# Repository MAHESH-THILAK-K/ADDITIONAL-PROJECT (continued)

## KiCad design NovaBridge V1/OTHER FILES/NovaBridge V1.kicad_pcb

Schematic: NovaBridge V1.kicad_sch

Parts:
C1: 10uF; C_1206_3216Metric_Pad1.33x1.80mm_HandSolder
C2: 22uF; C_1206_3216Metric_Pad1.33x1.80mm_HandSolder
C3: 100nF; C_1206_3216Metric_Pad1.33x1.80mm_HandSolder
D1: LED; LED_1206_3216Metric_Pad1.42x1.75mm_HandSolder
J1, J2: Conn_02x09_Odd_Even; PinSocket_2x09_P2.54mm_Vertical
J3, J4: Conn_01x08_Female; PinSocket_1x08_P2.54mm_Vertical
J5: +/- rail; PinHeader_2x06_P2.54mm_Vertical
J6: Conn_01x03; PinHeader_1x03_P2.54mm_Vertical
Q1: MUN5214DW1; SOT-363_SC-70-6
R1: 2k; R_1206_3216Metric_Pad1.30x1.75mm_HandSolder
U1: AZ1117; SOT-223-3_TabPin2

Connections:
/#SU: J3.7
/+3.3v: J3.2
/+5v-in: J3.1, J6.1
/+5v-out: C1.1, J6.2, R1.2, U1.3 (VI)
/CLK: J1.15
/CMD: J1.16
/CTS: J4.8
/DCD: J4.2
/DSR: J4.4
/DTR: J4.3, Q1.1 (E1), Q1.5 (B2)
/ESP-RX: J2.13, J4.5
/ESP-TX: J2.15, J4.6
/GND: C1.2, C2.2, C3.2, D1.1 (K), J2.11, J2.18, J3.3, J5.2, J5.4, J5.6, J5.8, J5.10, J5.12, U1.1 (ADJ)
/IO2: J2.1
/IO4: J2.3
/IO5: J2.8
/IO12: J1.12
/IO13: J1.11
/IO14: J1.9
/IO15: J2.2
/IO16: J2.6
/IO17: J2.5
/IO18: J2.7
/IO19: J2.10
/IO21: J2.9
/IO22: J2.12
/IO23: J2.14
/IO25: J1.8
/IO26: J1.7
/IO27: J1.10
/IO32: J1.6
/IO33: J1.5
/IO34: J1.4
/IO35: J1.3
/R1: J4.1
/RST: J3.4
/RTS: J4.7, Q1.2 (B1), Q1.4 (E2)
/SD1: J1.17
/SD2: J1.14
/SD3: J1.13
/SDO: J1.18
/SU: J3.8
/SVN: J1.1
/SVP: J1.2
/VDD: C2.1, J2.17, J5.1, J5.3, J5.5, J5.7, J5.9, J5.11, U1.2 (VO)
/aIO2: J3.6
/aIO3: J3.5
unnamed: D1.2 (A), R1.1

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
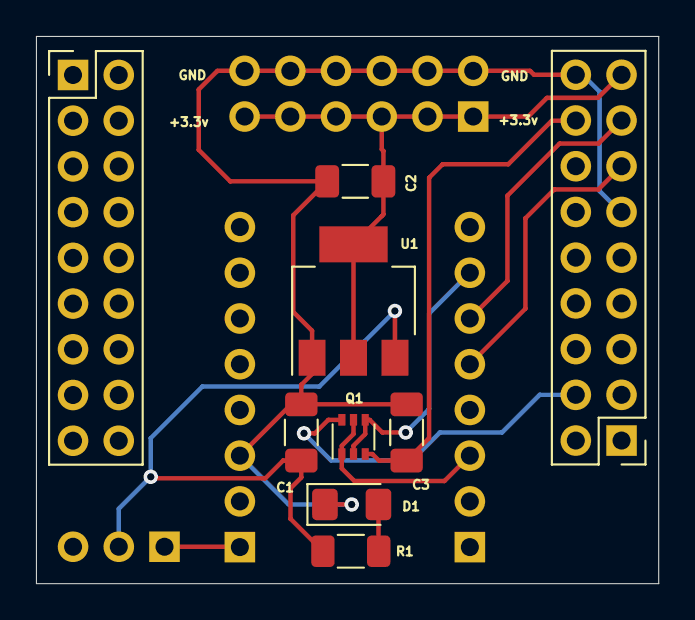
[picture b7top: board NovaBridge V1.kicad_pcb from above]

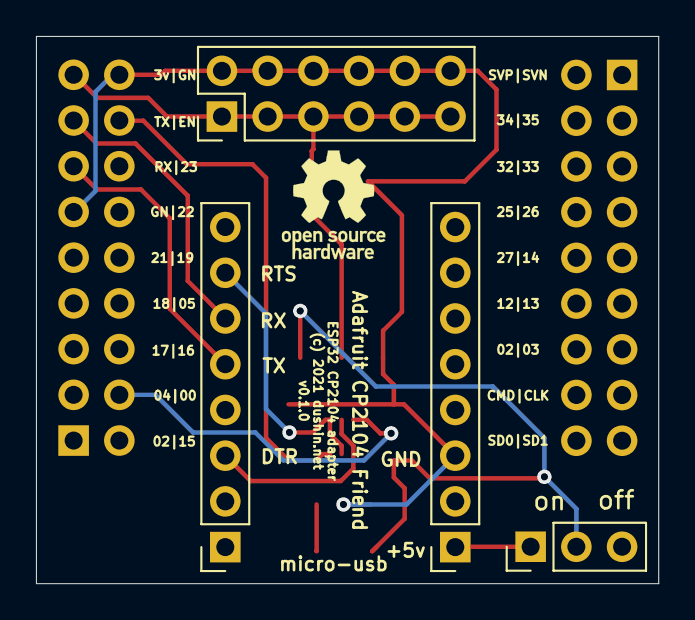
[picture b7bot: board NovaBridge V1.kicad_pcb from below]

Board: 2 copper layers, 34.6 x 30.4 mm, 13 parts (4 on the bottom side), 11 nets.

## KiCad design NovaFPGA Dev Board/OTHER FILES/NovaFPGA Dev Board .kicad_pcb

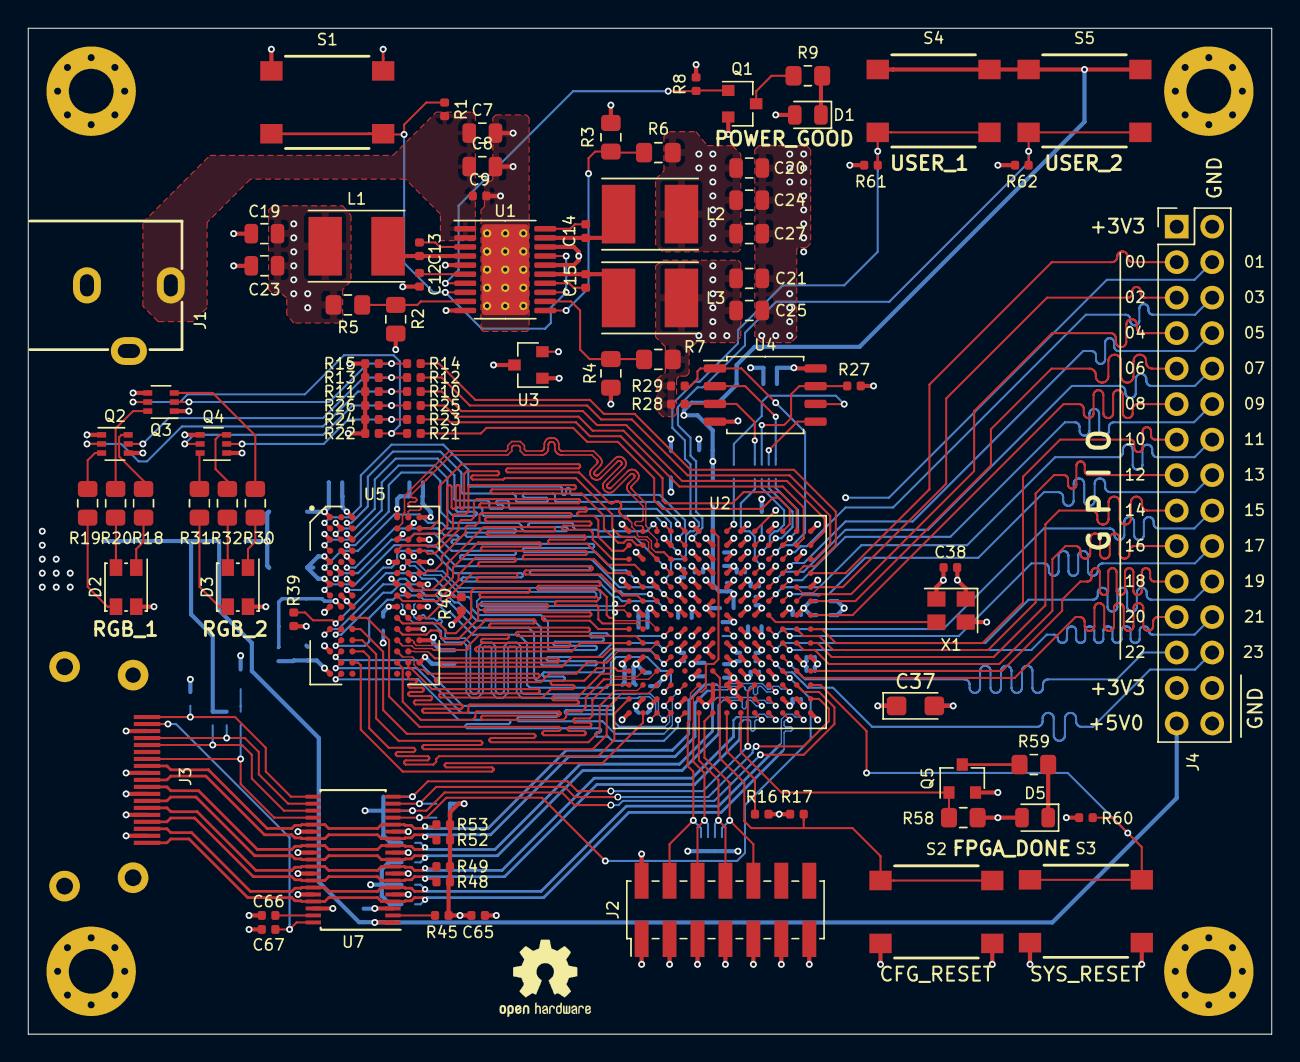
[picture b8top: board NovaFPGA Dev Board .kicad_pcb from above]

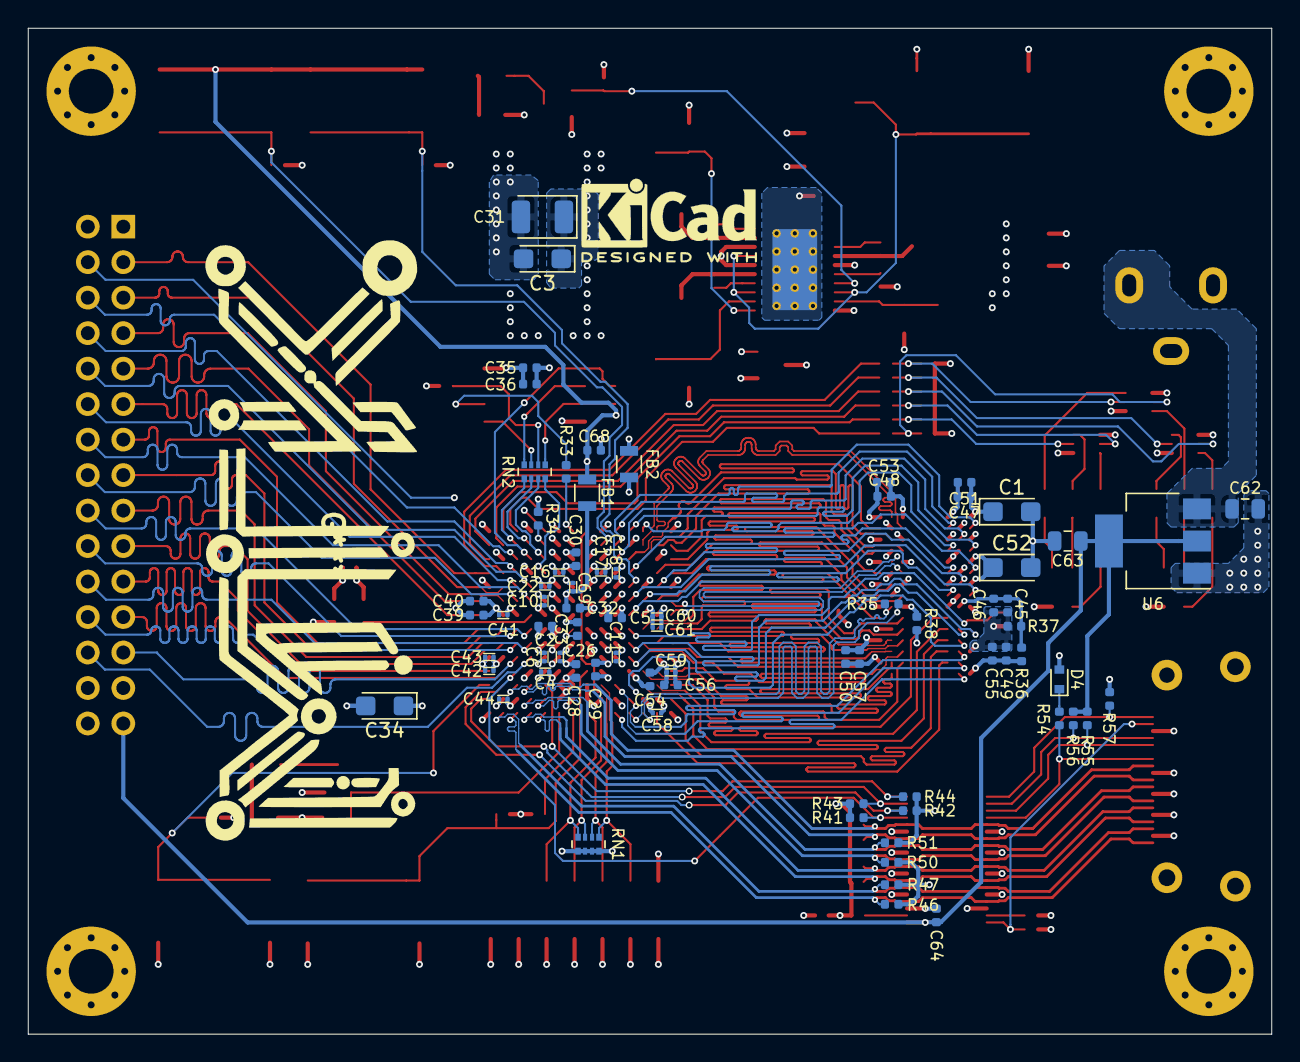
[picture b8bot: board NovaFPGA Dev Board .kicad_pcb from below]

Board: 4 copper layers, 89.0 x 72.0 mm, 169 parts (74 on the bottom side), 164 nets.

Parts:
C1, C3, C34, C37, C52: 47 uF; CP_EIA-3216-18_Kemet-A
C2, C5, C28, C29, C30, C39, C40, C54, C56, C68: 4.7 uF; C_0402_1005Metric
C4, C6, C10, C11, C16, C17, C18, C22, C26, C41, C42, C43, C44, C58, C59, C60, C61, C69: 0.47 uF; C_0201_0603Metric
C7, C8, C62: 10 uF; C_0805_2012Metric
C9, C13, C14, C15, C32, C33, C35, C38, C45, C47, C48, C49, C50, C64, C65, C66, C67: 0.1 uF; C_0402_1005Metric
C12, C36, C51, C53, C55, C57: 1 uF; C_0402_1005Metric
C19, C20, C21, C23, C24, C25, C27, C63: 22 uF; C_0805_2012Metric
C31: 100 uF; CP_EIA-3528-15_AVX-H
C46: 10 nF; C_0402_1005Metric
D1: POWER_GOOD; LED_0805_2012Metric
D2, D3: LED_RAGB; LED_Kingbright_AAA3528ESGCT
D4: BAS16XV2T1G; D_SOD-523
D5: FPGA_DONE; LED_0805_2012Metric
FB1, FB2: 600R; L_0805
H1, H2, H3, H4: MountingHole_Pad; MountingHole_3.2mm_M3_Pad_Via
J1: Barrel_Jack_Switch; PJ_102B
J2: XILINX_JTAG; PinHeader_2x07_P2.00mm_Vertical_SMD
J3: HDMI_A; hdmi_type_a_10029449-111RLF
J4: Conn_02x15_Odd_Even; PinHeader_2x15_P2.54mm_Vertical
L1, L2, L3: 2.2 uH; L_Taiyo-Yuden_NR-50xx_HandSoldering
Q1, Q5: DMN2020L; SOT-23
Q2, Q3, Q4: DMN63D8LDW; SOT-363_SC-70-6
R1, R8, R44: 100K; R_0402_1005Metric
R2, R3, R4: 2.2K; R_0805_2012Metric_Pad1.15x1.40mm_HandSolder
R5: 3.0K; R_0805_2012Metric_Pad1.15x1.40mm_HandSolder
R6, R9, R18, R30, R59: 680; R_0805_2012Metric_Pad1.15x1.40mm_HandSolder
R7: 7.36K; R_0805_2012Metric_Pad1.15x1.40mm_HandSolder
R10, R12, R14, R21, R23, R25, R55, R56: 2.2K; R_0402_1005Metric
R11, R13, R15, R22, R24, R26, R45, R57: 10K; R_0402_1005Metric
R16, R17, R27, R28, R29, R34, R38, R39, R40, R60, R61, R62: 4.75K; R_0402_1005Metric
R19, R20, R31, R32, R58: 330; R_0805_2012Metric_Pad1.15x1.40mm_HandSolder
R33, R46, R47, R48, R49, R50, R51, R52, R53: 49.9; R_0402_1005Metric
R35: 100; R_0402_1005Metric
R36, R37: 1.0K; R_0402_1005Metric
R41, R42, R43: 47K; R_0402_1005Metric
R54: 27K; R_0402_1005Metric
RN1: 10K; R_Array_Convex_4x0402
RN2: 49.9; R_Array_Convex_4x0402
S1: PWR_OFF; B3FS_1010P
S2: CFG_RESET; B3FS_1010P
S3: SYS_RESET; B3FS_1010P
S4: USER_1; B3FS_1010P
S5: USER_2; B3FS_1010P
U1: TPS65581; HTSSOP-20-1EP_4.4x6.5mm_P0.65mm_EP3.4x6.5mm_Mask2.75x3.43mm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
U2: XC7S50-FTGB196; Xilinx_FTGB196
U3: REF3012; SOT-23
U4: QSPI_Flash_SOIC8; SOIC-8_5.275x5.275mm_P1.27mm
U5: MT47H128M16XX; BGA-84_9x15_9.0x12.5mm
U6: AZ1117-5.0; SOT-223-3_TabPin2
U7: TPD12S521; TSSOP-38_4.4x9.7mm_P0.5mm
X1: DSC61XX; Oscillator_SMD_Abracon_ASE-4Pin_3.2x2.5mm

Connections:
+1V0: C3.1, C5.1, C11.1, C16.1, C17.1, C18.1, C20.1, C22.1, C24.1, C26.1, C27.1, C28.1, C29.1, C30.1, C31.1, L2.2, R6.1, U2.D6, U2.D8, U2.E5, U2.E7, U2.E9, U2.F6, U2.G5, U2.G9, U2.H6, U2.J5, U2.J9, U2.K6, U2.K8
+1V8: C1.1, C2.1, C4.1, C6.1, C10.1, C19.1, C23.1, C47.1, C48.1, C49.1, C50.1, C51.1, C52.1, C53.1, C54.1, C55.1, C56.1, C57.1, C58.1, C59.1, C60.1, C61.1, C68.1, FB1.2, L1.2, R5.1, R36.2, S4.1, S4.2, S5.1, S5.2, U2.F10, U2.G2, U2.H10, U2.K2, U2.K10, U2.L9, U2.N2, U5.A1, U5.A9, U5.C1, U5.C3, U5.C7, U5.C9, U5.E1, U5.E9, U5.G1, U5.G3, U5.G7, U5.G9, U5.J1, U5.J9, U5.M9, U5.R1
+1V8A: C32.1, C69.1, FB1.1, U2.F8
+3V3: C21.1, C25.1, C34.1, C35.1, C36.1, C37.1, C38.1, C39.1, C40.1, C41.1, C42.1, C43.1, C44.1, C65.1, D1.2, D2.2, D3.2, D4.2, D5.2, J2.2, J4.1, J4.27, L3.2, R7.1, R8.2, R16.2, R17.2, R27.2, R28.2, R29.2, R34.1, R41.1, R42.1, R43.1, R44.1, R45.2, R46.1, R47.1, R48.1, R49.1, R50.1, R51.1, R52.1, R53.1, R58.2, R60.1, RN1.5, RN1.6, RN1.7, RN1.8, U2.G13, U2.K13, U2.M7, U2.N6, U2.N7, U2.N8, U2.N13, U3.1, U4.8, X1.1, X1.4
+5V: C63.1, C64.1, J4.29, R55.2, R56.2, U6.2, U7.1
+12V: C7.1, C8.1, C9.1, C62.2, J1.1, R1.2, U1.1, U1.2, U6.3
/Bank0_14/FPGA_DONE: Q5.1, R58.1, U2.P9
/Bank0_14/FPGA_PUDC: R34.2, U2.B10
/Bank0_14/INIT_B: R16.1, U2.P8
/Bank0_14/JTAG_TCK: J2.6, RN1.2, U2.A7
/Bank0_14/JTAG_TDI: J2.10, RN1.4, U2.P7
/Bank0_14/JTAG_TDO: J2.8, RN1.3, U2.P6
/Bank0_14/JTAG_TMS: J2.4, RN1.1, U2.M6
/Bank0_14/PROGRAM_B: R17.1, S2.1, S2.2, U2.L7
/Bank0_14/RGB1_B: R14.2, U2.D13
/Bank0_14/RGB1_G: R12.2, U2.C14
/Bank0_14/RGB1_R: R10.2, U2.B14
/Bank0_14/RGB2_B: R25.2, U2.B13
/Bank0_14/RGB2_G: R23.2, U2.A13
/Bank0_14/RGB2_R: R21.2, U2.A12
/Bank0_14/SPI_CS: R29.1, U2.C11, U4.1
/Bank0_14/SPI_DQ0: RN2.3, U4.5
/Bank0_14/SPI_DQ1: RN2.4, U4.2
/Bank0_14/SPI_DQ2: R28.1, RN2.1, U4.3
/Bank0_14/SPI_DQ3: R27.1, RN2.2, U4.7
/Bank0_14/SPI_F_DQ0: RN2.6, U2.B11
/Bank0_14/SPI_F_DQ1: RN2.5, U2.B12
/Bank0_14/SPI_F_DQ2: RN2.8, U2.D10
/Bank0_14/SPI_F_DQ3: RN2.7, U2.C10
/Bank0_14/SPI_F_SCLK: R33.1, U2.A8
/Bank0_14/SPI_SCLK: R33.2, U4.6
/Bank0_14/SYSCLK: U2.G11, X1.3
/Bank0_14/SYSRESET: R60.2, S3.1, S3.2, U2.M14
/Bank34/DDR2_A0: U2.J2, U5.M8
/Bank34/DDR2_A1: U2.M3, U5.M3
/Bank34/DDR2_A2: U2.J1, U5.M7
/Bank34/DDR2_A3: U2.N4, U5.N2
/Bank34/DDR2_A4: U2.J3, U5.N8
/Bank34/DDR2_A5: U2.N1, U5.N3
/Bank34/DDR2_A6: U2.K3, U5.N7
/Bank34/DDR2_A7: U2.M5, U5.P2
/Bank34/DDR2_A8: U2.L1, U5.P8
/Bank34/DDR2_A9: U2.P2, U5.P3
/Bank34/DDR2_A10: U2.M4, U5.M2
/Bank34/DDR2_A11: U2.L3, U5.P7
/Bank34/DDR2_A12: U2.P5, U5.R2
/Bank34/DDR2_A13: U2.L2, U5.R8
/Bank34/DDR2_BA0: U2.K4, U5.L2
/Bank34/DDR2_BA1: U2.M2, U5.L3
/Bank34/DDR2_BA2: U2.J4, U5.L1
/Bank34/DDR2_CAS: U2.H1, U5.L7
/Bank34/DDR2_CK+: R35.1, U2.P4, U5.J8
/Bank34/DDR2_CK-: R35.2, U2.P3, U5.K8
/Bank34/DDR2_CKE: R39.2, U2.H4, U5.K2
/Bank34/DDR2_DM0: U2.E2, U5.F3
/Bank34/DDR2_DM1: U2.A5, U5.B3
/Bank34/DDR2_DQ0: U2.D2, U5.G8
/Bank34/DDR2_DQ1: U2.F4, U5.G2
/Bank34/DDR2_DQ2: U2.F2, U5.H7
/Bank34/DDR2_DQ3: U2.G4, U5.H3
/Bank34/DDR2_DQ4: U2.F3, U5.H1
/Bank34/DDR2_DQ5: U2.D1, U5.H9
/Bank34/DDR2_DQ6: U2.D4, U5.F1
/Bank34/DDR2_DQ7: U2.C1, U5.F9
/Bank34/DDR2_DQ8: U2.C3, U5.C8
/Bank34/DDR2_DQ9: U2.C5, U5.C2
/Bank34/DDR2_DQ10: U2.B2, U5.D7
/Bank34/DDR2_DQ11: U2.A3, U5.D3
/Bank34/DDR2_DQ12: U2.A4, U5.D1
/Bank34/DDR2_DQ13: U2.B1, U5.D9
/Bank34/DDR2_DQ14: U2.B5, U5.B1
/Bank34/DDR2_DQ15: U2.C4, U5.B9
/Bank34/DDR2_DQS0+: U2.G1, U5.F7
/Bank34/DDR2_DQS0-: U2.F1, U5.E8
/Bank34/DDR2_DQS1+: U2.B3, U5.B7
/Bank34/DDR2_DQS1-: U2.A2, U5.A8
/Bank34/DDR2_ODT: R40.2, U2.H3, U5.K9
/Bank34/DDR2_RAS: U2.H2, U5.K7
/Bank34/DDR2_WE: U2.M1, U5.K3
/Bank34/USER_1: R61.1, S4.3, S4.4, U2.E4
/Bank34/USER_2: R62.1, S5.3, S5.4, U2.B6
/Externals/HDMI_C_5V: C67.2, J3.18, U7.38
/Externals/HDMI_C_CEC: J3.13, R54.1, U7.23
/Externals/HDMI_C_HPD: J3.19, R57.1, U7.20
/Externals/HDMI_C_SCL: J3.15, R55.1, U7.22
/Externals/HDMI_C_SDA: J3.16, R56.1, U7.21
/Power/PGOOD: Q1.1, R8.1, U1.7
/Power/SW1: C13.1, L1.1, U1.4
/Power/SW2: C14.1, L2.1, U1.19
/Power/SW3: C15.1, L3.1, U1.15
ADC_REF: C33.1, U2.H8, U3.2
GND: C1.2, C2.2, C3.2, C4.2, C5.2, C6.2, C7.2, C8.2, C9.2, C10.2, C11.2, C12.2, C16.2, C17.2, C18.2, C19.2, C20.2, C21.2, C22.2, C23.2, C24.2, C25.2, C26.2, C27.2, C28.2, C29.2, C30.2, C31.2, C34.2, C35.2, C36.2, C37.2, C38.2, C39.2, C40.2, C41.2, C42.2, C43.2, C44.2, C45.2, C46.2, C47.2, C48.2, C49.2, C50.2, C51.2, C52.2, C53.2, C54.2, C55.2, C56.2, C57.2, C58.2, C59.2, C60.2, C61.2, C62.1, C63.2, C64.2, C65.2, C66.1, C67.1, C68.2, C69.2, FB2.2, H1.1, H2.1, H3.1, H4.1, J1.2, J2.1, J2.3, J2.5, J2.7, J2.9, J2.11, J2.13, J3.2, J3.5, J3.8, J3.11, J3.17, J3.SH, J4.2, J4.28, J4.30, Q1.2, Q2.1, Q2.4, Q3.1, Q3.4, Q4.1, Q4.4, Q5.2, R2.2, R3.2, R4.2, R11.2, R13.2, R15.2, R22.2, R24.2, R26.2, R37.1, R38.1, R39.1, R40.1, R57.2, R61.2, R62.2, S1.1, S1.2, S2.3, S2.4, S3.3, S3.4, U1.5, U1.10, U1.16, U1.18, U1.21, U2.A1, U2.A6, U2.A9, U2.A11, U2.A14, U2.B4, U2.B7, U2.B8, U2.B9, U2.C2, U2.C6, U2.C7, U2.C8, U2.C9, U2.C13, U2.D5, U2.D7, U2.D9, U2.D11, U2.E1, U2.E3, U2.E6, U2.E8, U2.E10, U2.E14, U2.F5, U2.F9, U2.G3, U2.G6, U2.G10, U2.G12, U2.H5, U2.H9, U2.J6, U2.J7, U2.J8, U2.J10, U2.K1, U2.K5, U2.K7, U2.K9, U2.K14, U2.L4, U2.L6, U2.L8, U2.L10, U2.L11, U2.M8, U2.M9, U2.N3, U2.N5, U2.N9, U2.N12, U2.P1, U2.P14, U3.3, U4.4, U5.A3, U5.A7, U5.B2, U5.B8, U5.D2, U5.D8, U5.E3, U5.E7, U5.F2, U5.F8, U5.H2, U5.H8, U5.J3, U5.J7, U5.N1, U5.P9, U6.1, U7.3, U7.5, U7.8, U7.11, U7.14, U7.25, U7.28, U7.31, U7.34, U7.36, X1.2
GNDA: C32.2, C33.2, FB2.1, U2.F7, U2.G7, U2.G8, U2.H7
GPIO_0: J4.3, U2.D14
GPIO_1: J4.4, U2.A10
GPIO_2: J4.5, U2.E13
GPIO_3: J4.6, U2.C12
GPIO_4: J4.7, U2.F13
GPIO_5: J4.8, U2.D12
GPIO_6: J4.9, U2.F14
GPIO_7: J4.10, U2.E11
GPIO_8: J4.11, U2.G14
GPIO_9: J4.12, U2.E12
GPIO_10: J4.13, U2.H14
GPIO_11: J4.14, U2.F11
GPIO_12: J4.15, U2.H13
GPIO_13: J4.16, U2.F12
GPIO_14: J4.17, U2.J14
GPIO_15: J4.18, U2.H11
GPIO_16: J4.19, U2.J13
GPIO_17: J4.20, U2.H12
GPIO_18: J4.21, U2.L14
GPIO_19: J4.22, U2.J11
GPIO_20: J4.23, U2.L13
GPIO_21: J4.24, U2.J12
GPIO_22: J4.25, U2.K12
GPIO_23: J4.26, U2.K11
HDMI_CEC: R41.2, U2.L12, U7.16
HDMI_CLK+: J3.10, R52.2, U2.M11, U7.13, U7.26
HDMI_CLK-: J3.12, R53.2, U2.M12, U7.15, U7.24
HDMI_D0+: J3.7, R50.2, U2.N10, U7.10, U7.29
HDMI_D0-: J3.9, R51.2, U2.N11, U7.12, U7.27
HDMI_D1+: J3.4, R48.2, U2.P10, U7.7, U7.32
HDMI_D1-: J3.6, R49.2, U2.P11, U7.9, U7.30
HDMI_D2+: J3.1, R46.2, U2.P12, U7.4, U7.35
HDMI_D2-: J3.3, R47.2, U2.P13, U7.6, U7.33
HDMI_HPD: R44.2, U2.M10, U7.19
HDMI_SCL: R42.2, U2.M13, U7.17
HDMI_SDA: R43.2, U2.N14, U7.18
unnamed: C12.1, U1.6
unnamed: C13.2, U1.3
unnamed: C14.2, U1.20
unnamed: C15.2, U1.14
unnamed: C45.1, C46.1, R36.1, R37.2, U5.J2
unnamed: C66.2, U7.37
unnamed: D1.1, R9.2
unnamed: D2.1, R18.1
unnamed: D2.3, R19.1
unnamed: D2.4, R20.1
unnamed: D3.1, R30.1
unnamed: D3.3, R31.1
unnamed: D3.4, R32.1
unnamed: D4.1, R54.2
unnamed: D5.1, R59.2
unnamed: Q1.3, R9.1
unnamed: Q2.2, R10.1, R11.1
unnamed: Q2.3, R19.2
unnamed: Q2.5, R12.1, R13.1
unnamed: Q2.6, R18.2
unnamed: Q3.2, R14.1, R15.1
unnamed: Q3.3, R30.2
unnamed: Q3.5, R21.1, R22.1
unnamed: Q3.6, R20.2
unnamed: Q4.2, R23.1, R24.1
unnamed: Q4.3, R32.2
unnamed: Q4.5, R25.1, R26.1
unnamed: Q4.6, R31.2
unnamed: Q5.3, R59.1
unnamed: R1.1, S1.3, S1.4, U1.8, U1.13, U1.17
unnamed: R2.1, R5.2, U1.9
unnamed: R3.1, R6.2, U1.11
unnamed: R4.1, R7.2, U1.12
unnamed: R38.2, U5.L8
unnamed: R45.1, U7.2
